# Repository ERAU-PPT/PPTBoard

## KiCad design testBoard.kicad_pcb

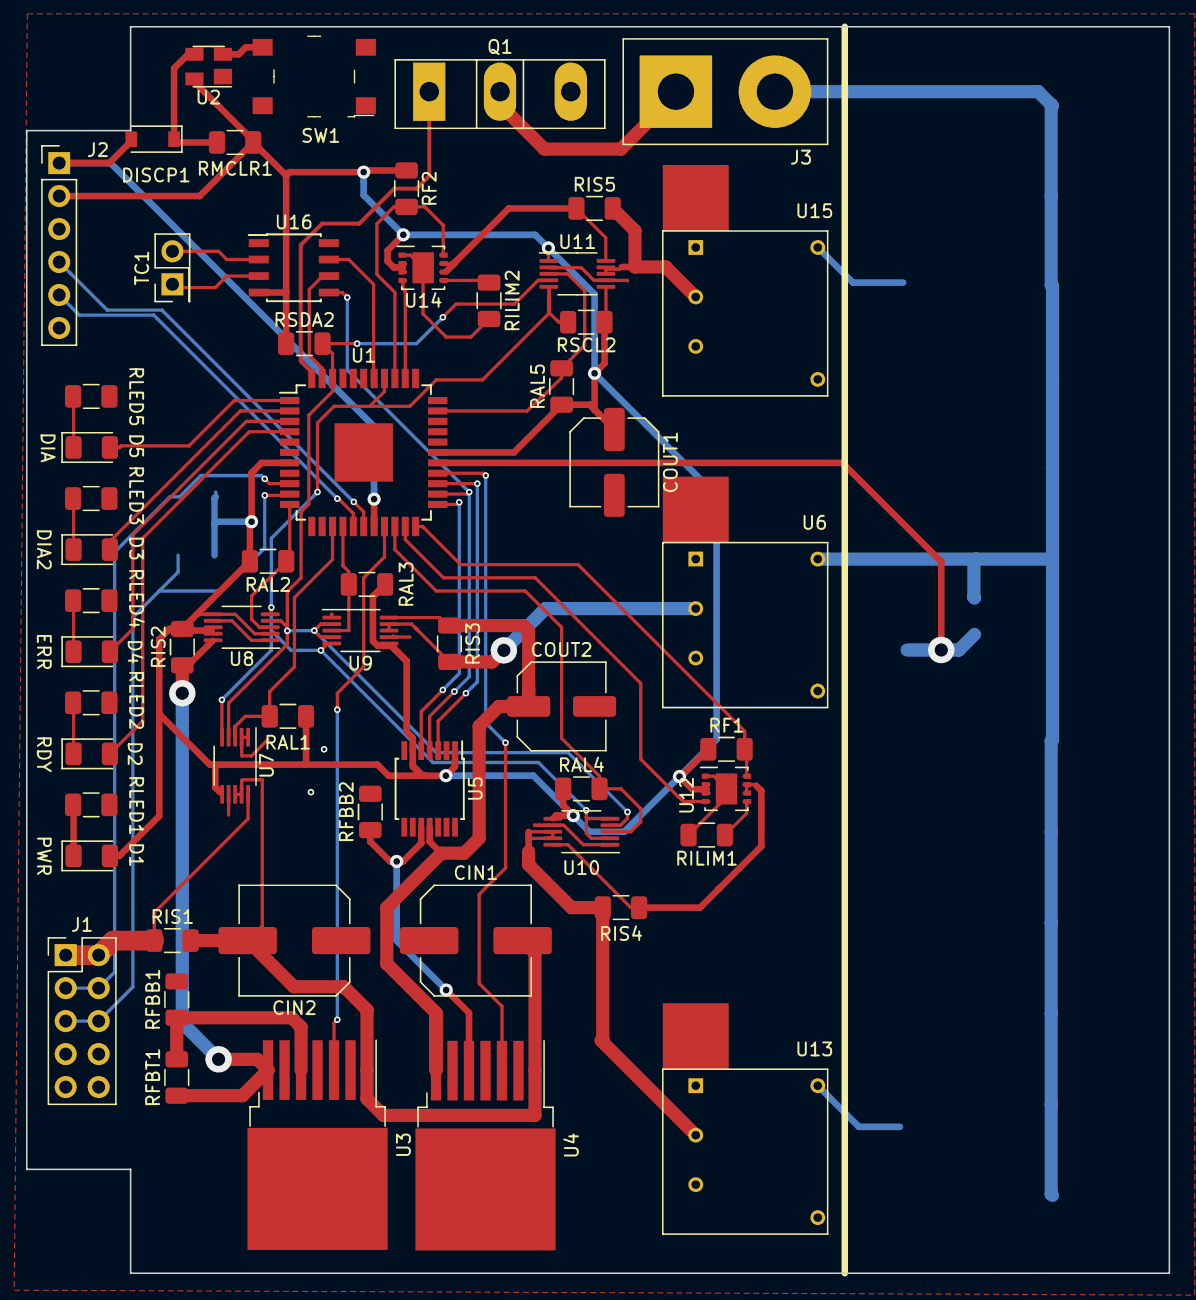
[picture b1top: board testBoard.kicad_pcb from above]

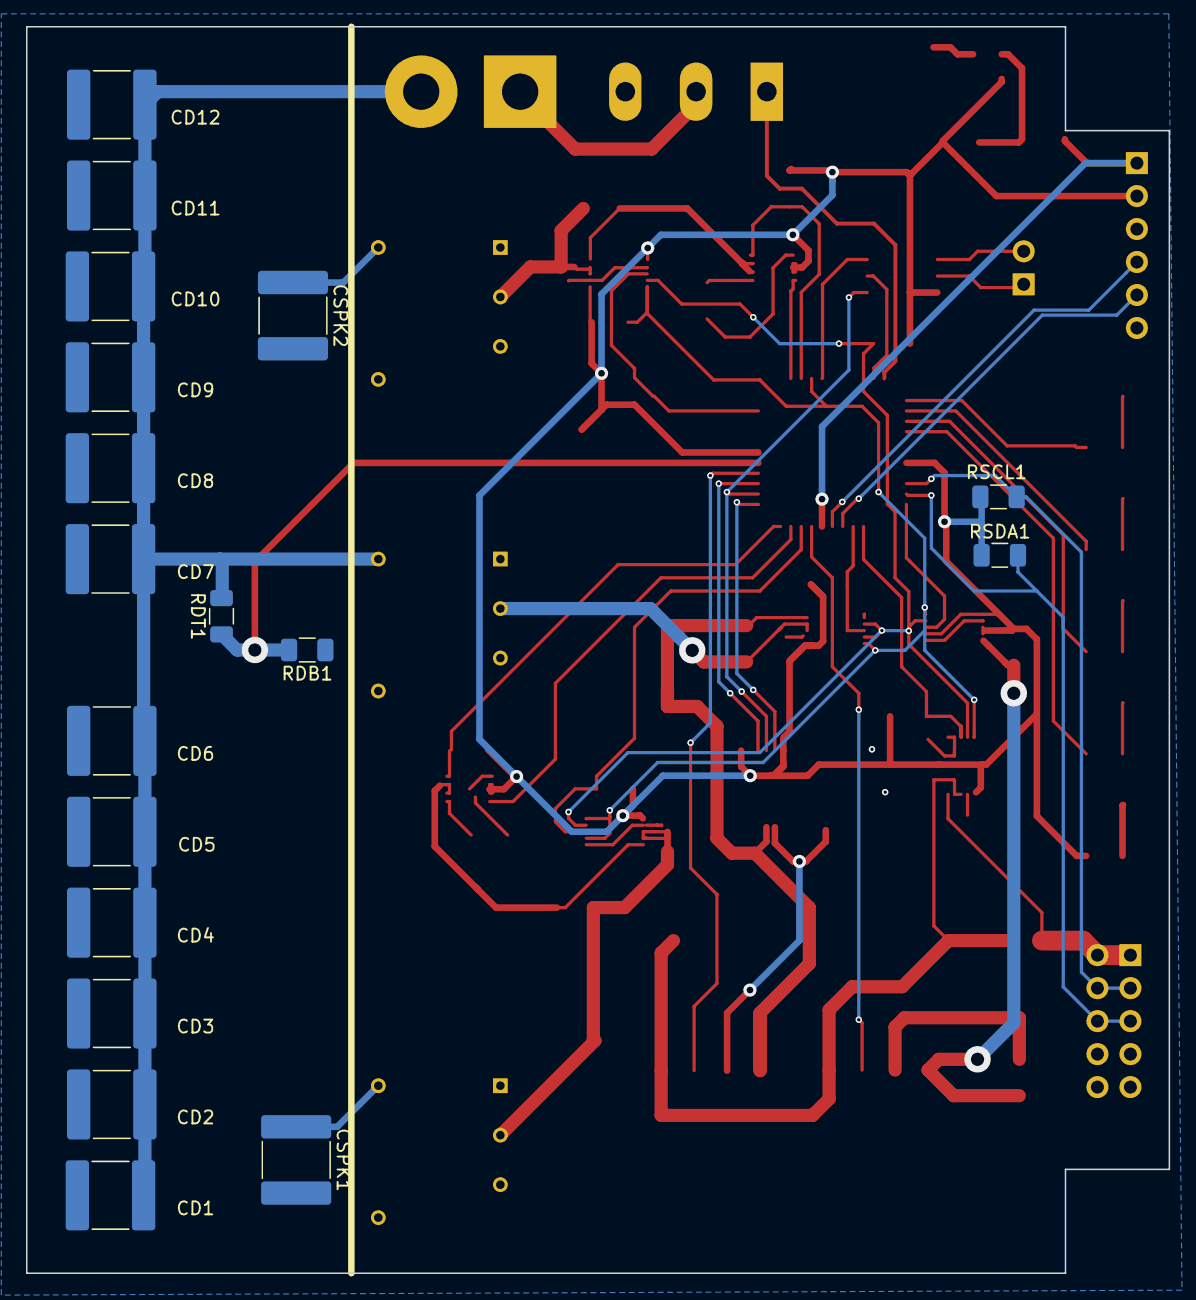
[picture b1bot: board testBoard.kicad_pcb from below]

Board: 2 copper layers, 88.0 x 96.0 mm, 75 parts (18 on the bottom side), 57 nets.

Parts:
CD1, CD2, CD3, CD4, CD5, CD6, CD7, CD8, CD9, CD10, CD11, CD12: 0.47u; C_2220_5650Metric
CIN1, CIN2: 22u; C_Elec_8x10.2
COUT1, COUT2: 330u; C_Elec_6.3x7.7
CSPK1, CSPK2: 2200p; C_2220_5650Metric
D1: PWR; LED_1206_3216Metric
D2: RDY; LED_1206_3216Metric
D3: DIA2; LED_1206_3216Metric
D4: ERR; LED_1206_3216Metric
D5: DIA; LED_1206_3216Metric
DISCP1: DIODE; D_SOD-123
J1: Conn_02x05_Odd_Even; PinHeader_2x05_P2.54mm_Vertical
J2: Conn_01x06; PinHeader_1x06_P2.54mm_Vertical
J3: Thruster_Connection; SolderWirePad_1x02_P0.220in_Drill0.110in
Q1: SCT2450KEC; TO-247-3_Vertical
RAL1, RAL2, RAL3, RAL4, RAL5: 4.7k; R_1206_3216Metric
RDB1: 500K; R_1206_3216Metric
RDT1: 100M; R_1206_3216Metric
RF1, RF2: 100k; R_1206_3216Metric
RFBB1, RFBB2: 1.87k; R_1206_3216Metric
RFBT1: 9.76k; R_1206_3216Metric
RILIM1, RILIM2: 100k; R_1206_3216Metric
RIS1, RIS2, RIS3, RIS4, RIS5: 0.01; R_1206_3216Metric
RLED1, RLED2, RLED3, RLED4, RLED5: 100; R_1206_3216Metric
RMCLR1: 4.7k; R_1206_3216Metric
RSCL1, RSCL2: 4.7k; R_1206_3216Metric
RSDA1, RSDA2: 4.7k; R_1206_3216Metric
SW1: PTS645SM43SMTR92_LFS; Switch_Tactile_SMD_6x6mm_PTS645
TC1: Thermocouple; PinHeader_2x01_P2.54mm_Vertical
U1: PIC18F47K40; TQFP-44-1EP_10x10mm_P0.8mm_EP4.5x4.5mm
U2: MAX6816; SOT-143
U3, U4: WPMDM171050601; TO-263-7_TabPin8
U5: MAX5483; TSSOP-14_4.4x5mm_P0.65mm
U6: EMCO-Q10-5; EMCO_Q_2.5-5kV-Shielded
U7, U8, U9, U10, U11: INA233; VSSOP-10_3x3mm_P0.5mm
U12, U14: TPS2557; Texas_S-PVSON-N8
U13, U15: EMCO-Q50-5; EMCO_Q_2.5-5kV-Shielded
U16: MAX6675; SOIC-8_3.9x4.9mm_P1.27mm

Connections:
/CAP_BANK_POSITIVE: CD1.1, CD2.1, CD3.1, CD4.1, CD5.1, CD6.1, CD7.1, CD8.1, CD9.1, CD10.1, CD11.1, CD12.1, J3.2, RDT1.2, U6.3
/DBNC_DDE_PRTCTD: DISCP1.1, RMCLR1.2, U2.3
/MCLR_BTTN: SW1.4, U2.2
/PWR_LED: D1.1, RLED1.2
/R_DIA: D5.1, RLED5.2
/R_DIA2: D3.1, RLED3.2
/R_ERR: D4.1, RLED4.2
/R_RDY: D2.1, RLED2.2
/SPK1: CSPK1.1, U13.3
/SPK2: CSPK2.1, U15.3
/TC+: TC1.1, U16.3
/TC-: TC1.2, U16.2
/Thrust_Connector: J3.1, Q1.2
/U3-FB: RFBB1.1, RFBT1.2, U3.5
/U4_FB: RFBB2.1, U4.5, U5.10
/U6_VIN: RIS3.2, U6.2, U9.8, U9.9
/U7_DIAG_NET: J1.1, J1.2, RIS1.1, U7.10
/U12_ILIM: RILIM1.1, U12.5
/U12_VOUT: RIS4.2, U10.10, U12.6, U12.7
/U13_VIN: RIS4.1, U10.8, U10.9, U13.2
/U14_ILIM: RILIM2.1, U14.5
/U14_OUT: RIS5.1, U11.10, U14.6, U14.7
/U15_VIN: RIS5.2, U11.8, U11.9, U15.2
DIA2_LED: D3.2, U1.2
DIA_LED: D5.2, U1.1
ERR_LED: D4.2, U1.3
GND: CD1.2, CD2.2, CD3.2, CD4.2, CD5.2, CD6.2, CD7.2, CD8.2, CD9.2, CD10.2, CD11.2, CD12.2, CIN1.1, CIN2.1, COUT1.2, COUT2.2, CSPK1.2, CSPK2.2, J1.9, J1.10, J2.3, Q1.3, RDB1.1, RFBB1.2, RFBB2.2, RILIM1.2, RILIM2.2, RLED1.1, RLED2.1, RLED3.1, RLED4.1, RLED5.1, SW1.2, U1.6, U1.29, U1.45, U2.1, U3.2, U3.4, U3.8, U4.2, U4.4, U4.8, U5.2, U5.14, U6.1, U6.4, U6.8, U7.1, U7.2, U7.7, U8.1, U8.7, U9.1, U9.7, U10.1, U10.7, U11.2, U11.7, U12.1, U12.9, U13.1, U13.4, U13.8, U14.1, U14.9, U15.1, U15.4, U15.8, U16.1
ICSPCLK: J2.5, U1.16
ICSPDAT: J2.4, U1.17
MCLR: DISCP1.2, J2.1, U1.18
PM_VIN: CIN1.2, CIN2.2, RIS1.2, U3.1, U4.1, U7.8, U7.9
RDY_LED: D2.2, U1.4
RE2: RDB1.2, RDT1.1, U1.27
SCL1: J1.3, J1.4, RSCL1.2, U1.9
SCL2: RSCL2.2, U1.37, U7.5, U8.5, U9.5, U10.2, U10.5, U11.5
SCLK: U1.24, U5.4, U16.5
SDA1: J1.5, J1.6, RSDA1.2, U1.10
SDA2: RSDA2.2, U1.42, U7.4, U8.4, U9.2, U9.4, U10.4, U11.4
THRUST_CONTROL: Q1.1, U1.44
U3_EN: U1.19, U3.3
U3_VOUT: RFBT1.1, RIS2.1, U3.7, U8.10
U4_EN: U1.26, U4.3
U4_VOUT: COUT2.1, RIS3.1, U4.7, U5.11, U9.10
U5_CS: U1.25, U5.3
U5_DIN: U1.23, U5.5
U7_ALERT: RAL1.1, U1.14, U7.3
U7_SD: U1.38, U16.7
U8_ALERT: RAL2.1, U1.11, U8.3
U9_ALERT: RAL3.1, U1.15, U9.3
U10_ALERT: RAL4.2, U1.20, U10.3
U11_ALERT: RAL5.2, U1.32, U11.3
U12_EN: U1.21, U12.4
U12_FAULT: RF1.2, U1.22, U12.8
U14_EN: U1.35, U14.4
U14_FAULT: RF2.1, U1.36, U14.8
U16_CS: U1.43, U16.6
VCC: COUT1.1, D1.2, J2.2, RAL1.2, RAL2.2, RAL3.2, RAL4.1, RAL5.1, RF1.1, RF2.2, RIS2.2, RMCLR1.1, RSCL1.1, RSCL2.1, RSDA1.1, RSDA2.1, U1.7, U1.28, U2.4, U5.1, U5.6, U7.6, U8.2, U8.6, U8.8, U8.9, U9.6, U10.6, U11.1, U11.6, U12.2, U12.3, U14.2, U14.3, U16.4

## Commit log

2019-02-07 Create gitignore
2019-02-07 Wipe for fresh start
2019-02-07 Started re-adding symbols
2019-02-07 Added PIC18 and MAX5483 changes
2019-02-12 started circuit design
2019-02-15 More schematic design
2019-04-07 Finished New Schematic of test board
2019-04-08 Added some footprint associations.
    Still needs J3, Q1, U15, U6. U13.
    U15, U6. U13 need custom made part.
2019-04-17 Added EMCO DC-DC Converter components
2019-04-18 Fix MOSFET, Add Wire Header
    *Fixed Q1 being a pin header instead of a mosfet.
    *Added footprint for the thick wires that attached from board to thruster, and added association to schematic
2019-04-18 Started work on PCB
2019-04-20 Added some netlist names
2019-04-20 Hopefully fixed pins
2019-04-20 Fix some pin naming inconsistencies
2019-04-21 Board design 1
2019-04-21 cleanup unused stuff
2019-04-26 update gitignore
2019-04-26 Final board design
